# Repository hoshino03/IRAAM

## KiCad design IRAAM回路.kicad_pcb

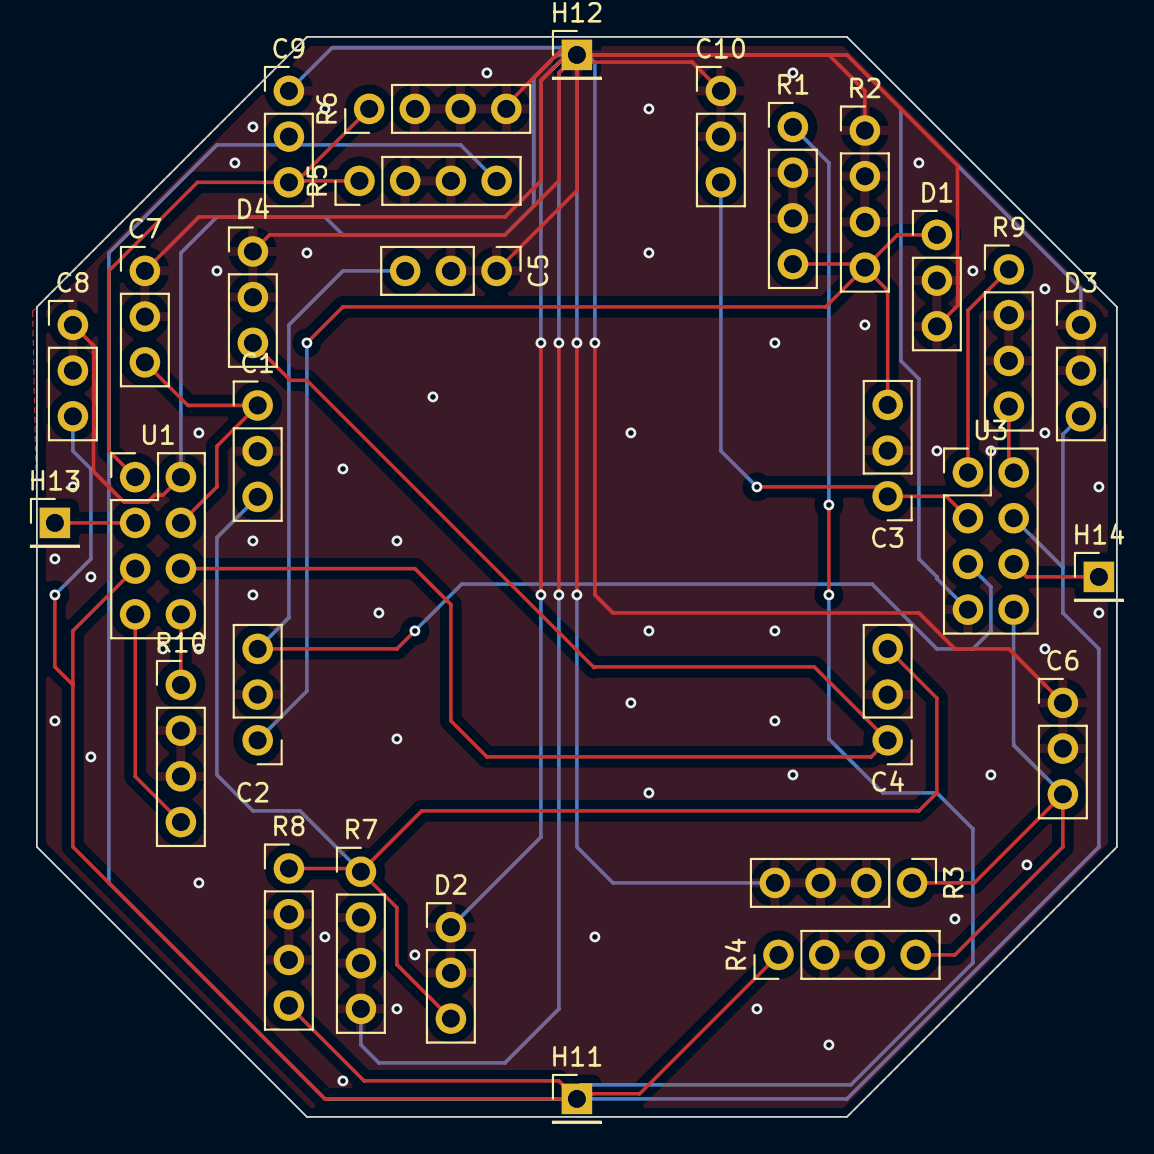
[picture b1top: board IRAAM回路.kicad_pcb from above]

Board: 2 copper layers, 60.0 x 60.0 mm, 40 parts (0 on the bottom side), 2 nets.

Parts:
C1, C2, C3, C4, C5, C6, C7, C8, C9, C10: C; PinHeader_1x03_P2.54mm_Vertical
D1, D2, D3, D4: D_Photo; PinHeader_1x03_P2.54mm_Vertical
H1, H2, H3, H4, H5, H6, H7, H8, H9, H10: MountingHole; MountingHole_3.2mm_M3
H11, H12, H13, H14: MountingHole_Pad; PinHeader_1x01_P2.54mm_Vertical
R1, R2, R3, R4, R5, R6, R7, R8, R9, R10: R; PinHeader_1x04_P2.54mm_Vertical
U1, U3: AD623ARZ; PinHeader_2x04_P2.54mm_Vertical

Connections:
GND: C1.2, C2.2, C3.2, C4.2, C5.1, C5.2, C6.1, C6.2, C7.1, C7.2, C8.1, C8.2, C9.1, C10.1, C10.2, D1.2 (A), D1.3, D2.1 (K), D2.2 (A), D3.1 (K), D3.2 (A), D4.1 (K), D4.2 (A), H12.1, R1.2, R1.3, R2.1, R2.2, R2.3, R3.2, R3.3, R3.4, R4.2, R4.3, R5.2, R5.3, R6.2, R6.3, R6.4, R7.2, R7.3, R7.4, R8.2, R8.3, R9.2, R9.3, R10.2, R10.3, U1.2 (-), U3.7 (Vs+)
unnamed: C1.1, C1.3, C2.1, C2.3, C3.1, C3.3, C4.1, C4.3, C5.3, C6.3, C7.3, C8.3, C9.2, C9.3, C10.3, D1.1 (K), D2.3, D3.3, D4.3, H11.1, H13.1, H14.1, R1.1, R1.4, R2.4, R3.1, R4.1, R4.4, R5.1, R5.4, R6.1, R7.1, R8.1, R9.1, R9.4, R10.1, R10.4, U1.1 (Rg), U1.3 (+), U1.5 (Ref), U1.6, U1.7 (Vs+), U1.8 (Rg), U3.1 (Rg), U3.2 (-), U3.3 (+), U3.4 (Vs-), U3.5 (Ref), U3.6, U3.8 (Rg)

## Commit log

2024-08-09 シーカー用プログラム(動かない)
    シリアルモニタで確認したら角度の計算はできてるけどサーボモータが動かない
2024-08-09 標的表裏
2024-08-09 シーカー回路図
2024-08-09 シーカーPCB
